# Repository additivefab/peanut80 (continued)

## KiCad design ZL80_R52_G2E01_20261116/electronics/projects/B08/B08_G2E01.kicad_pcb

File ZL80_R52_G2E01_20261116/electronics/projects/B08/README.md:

# B08 G2-E01

打开 B08_G2E01.kicad_pro。原理图是元件级候选；PCB有板框/孔/封装/网络及初排，尚无布线。

- Preserves R51 four-pin interface; bipolar supply required.
- Photodiode nominal reverse bias 5V. Current into cathode is sunk to negative bias; output is positive.
- 0..100uA input corresponds approximately 0..1V output. Confirm pickoff power before connecting.
- RF=10k / CF=100p is a ~159kHz feedback pole; reference and PMT channel delays must be aligned.
- This reference signal feeds B02 channel B through its own FDA; not directly a differential ADC input.

状态：NOT_RELEASED。仿真为有限模型证据；没有台架结果。

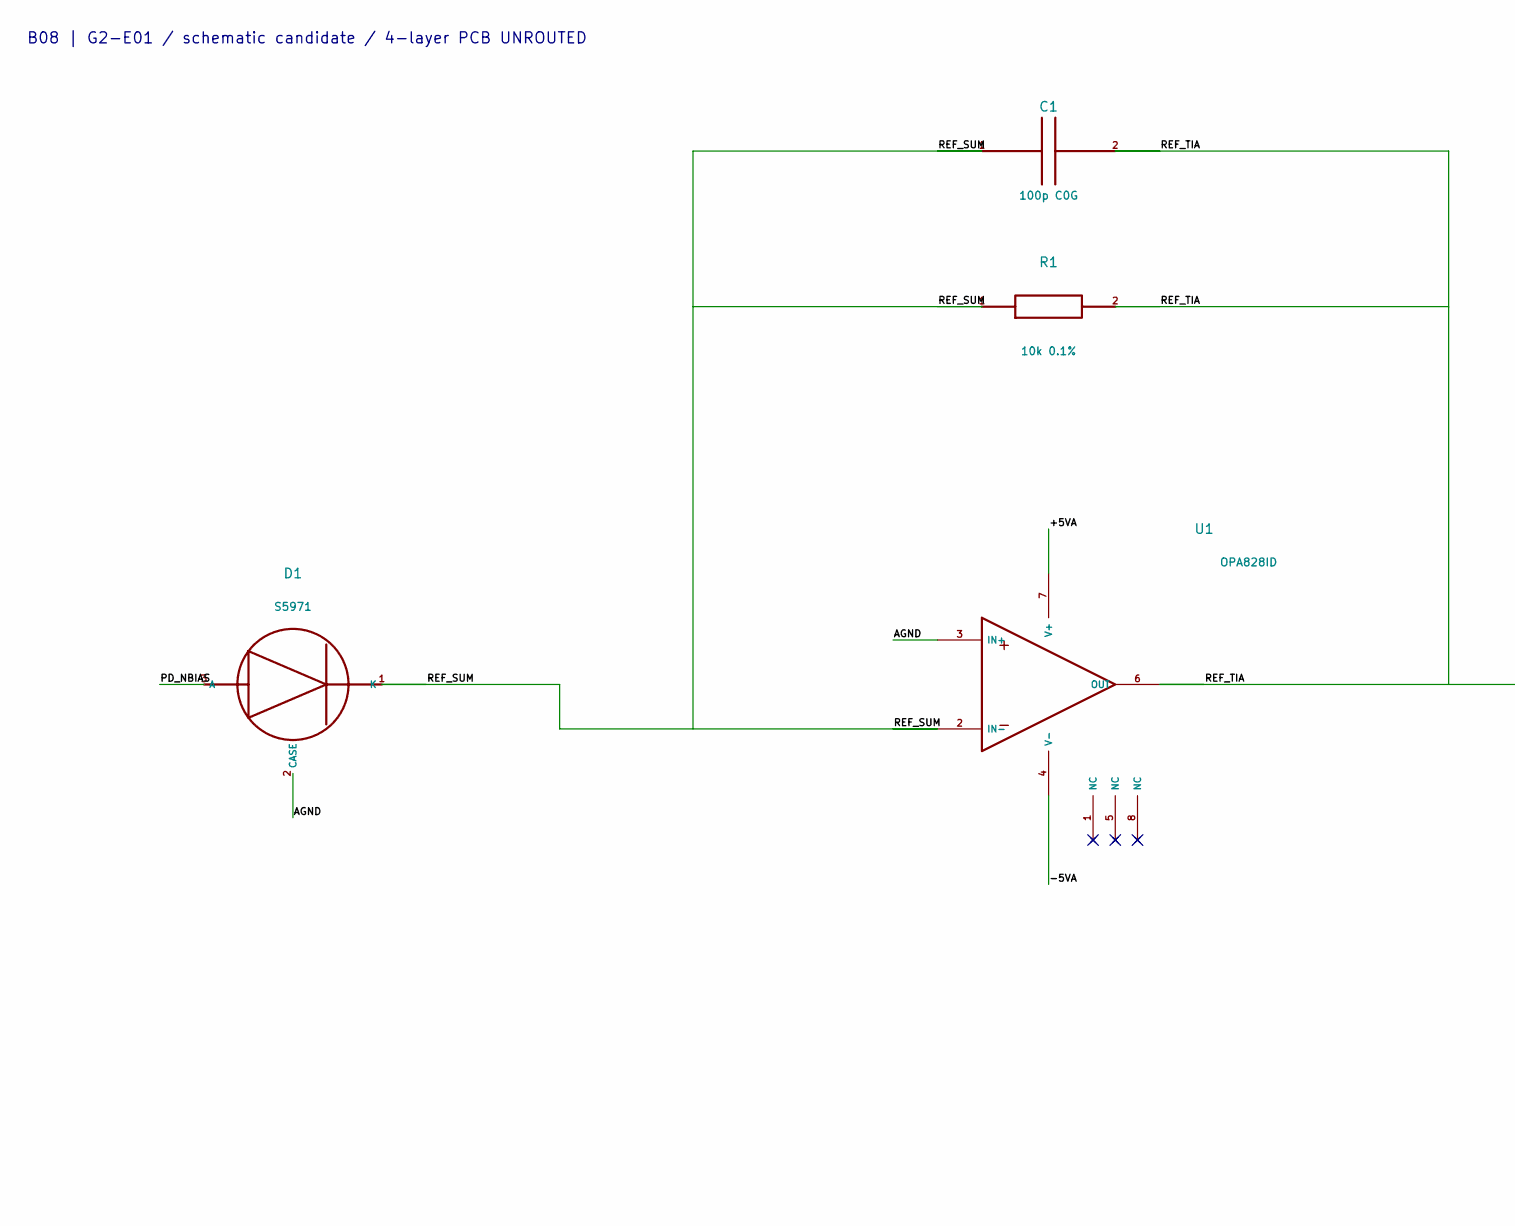
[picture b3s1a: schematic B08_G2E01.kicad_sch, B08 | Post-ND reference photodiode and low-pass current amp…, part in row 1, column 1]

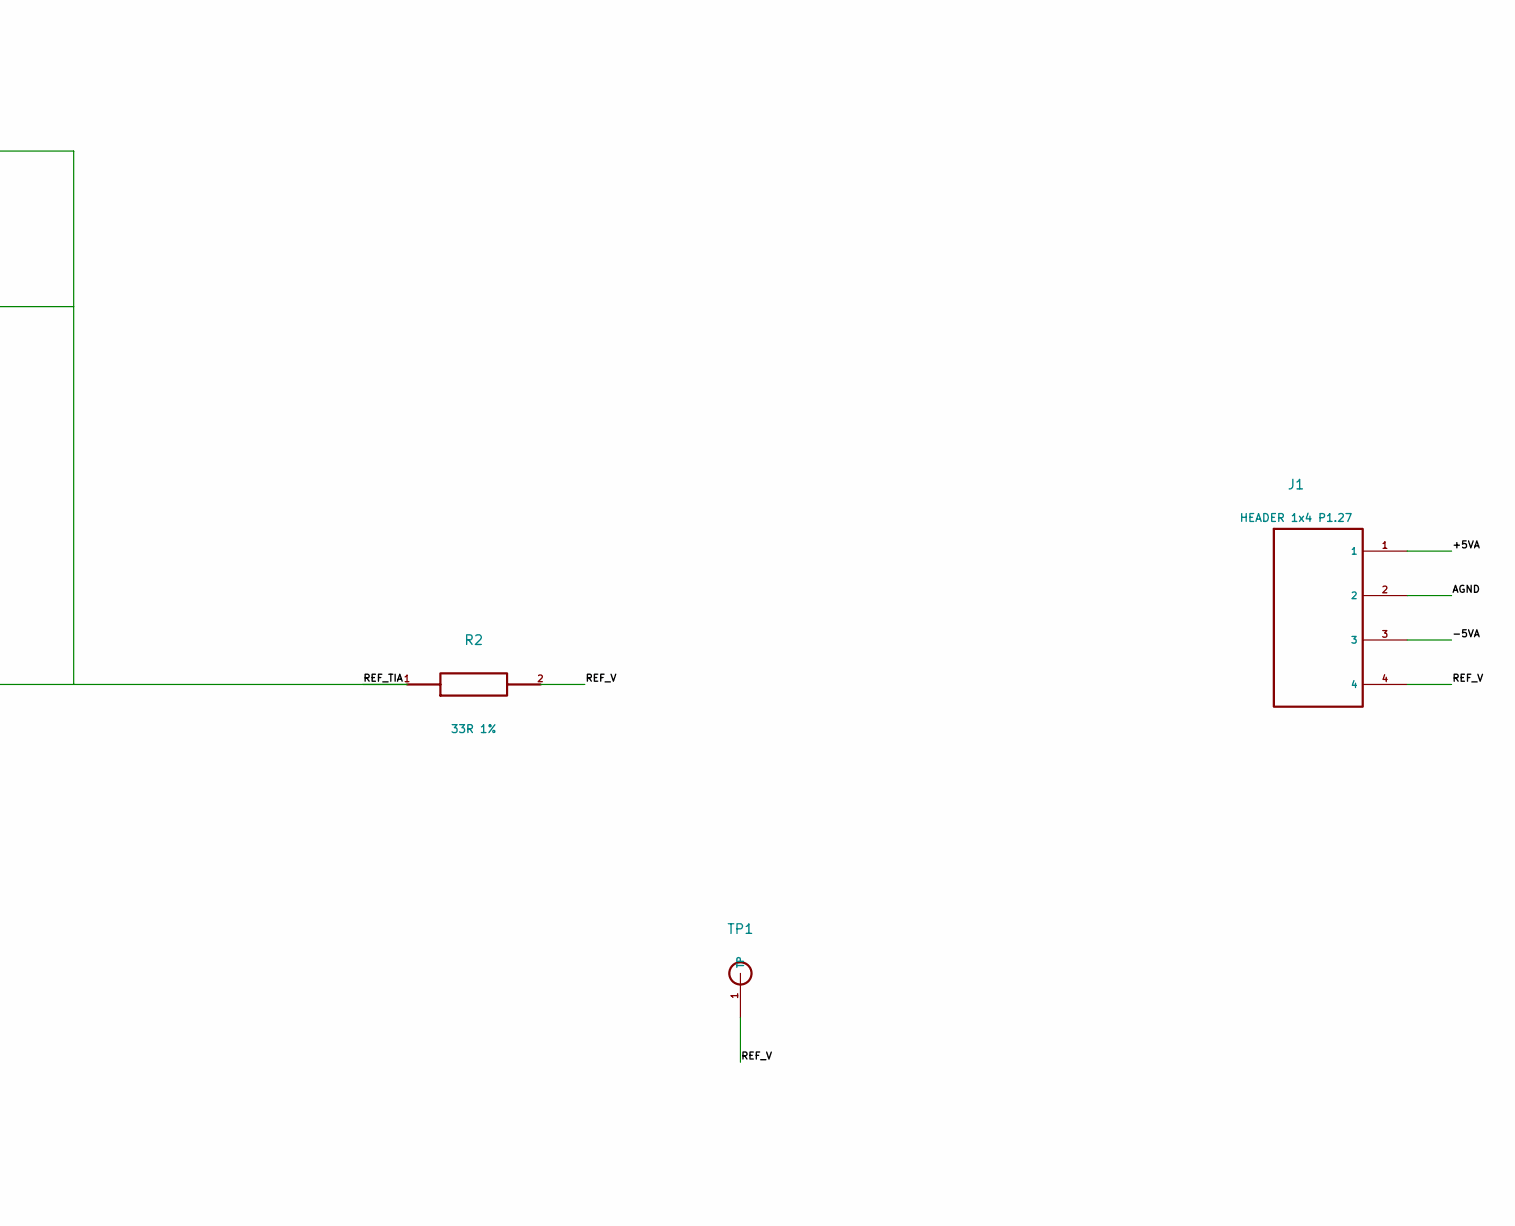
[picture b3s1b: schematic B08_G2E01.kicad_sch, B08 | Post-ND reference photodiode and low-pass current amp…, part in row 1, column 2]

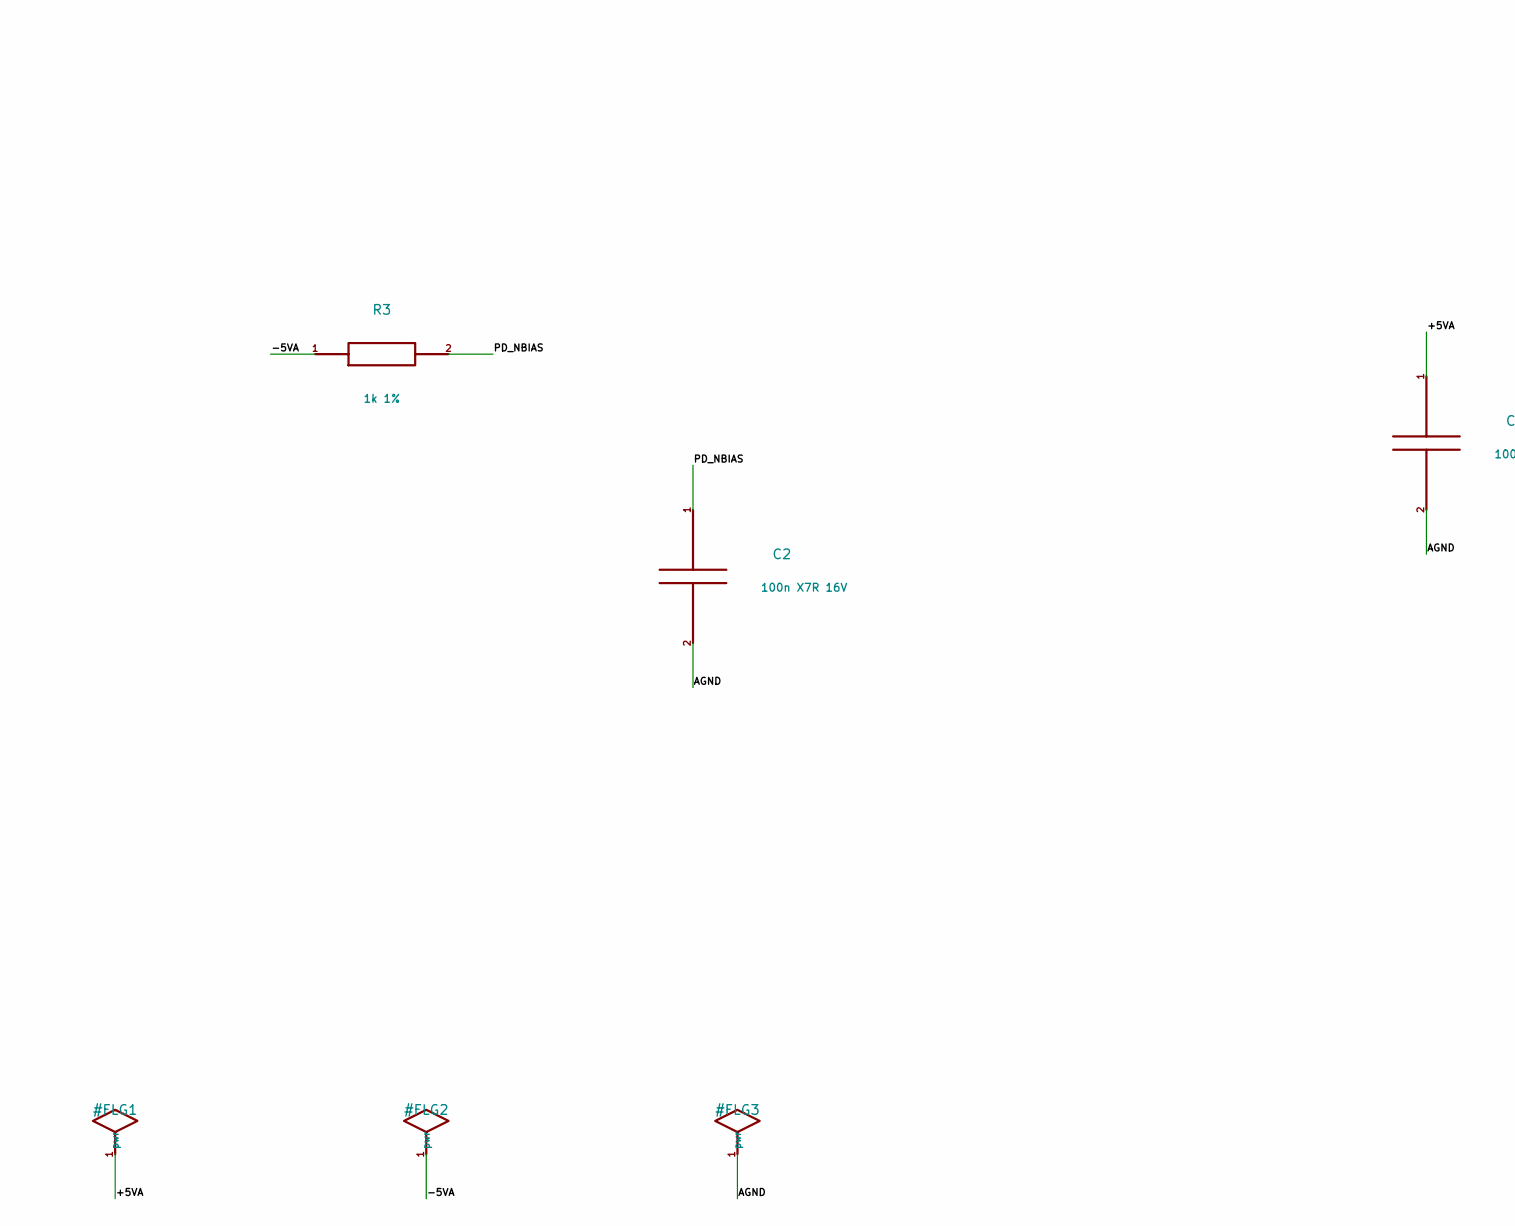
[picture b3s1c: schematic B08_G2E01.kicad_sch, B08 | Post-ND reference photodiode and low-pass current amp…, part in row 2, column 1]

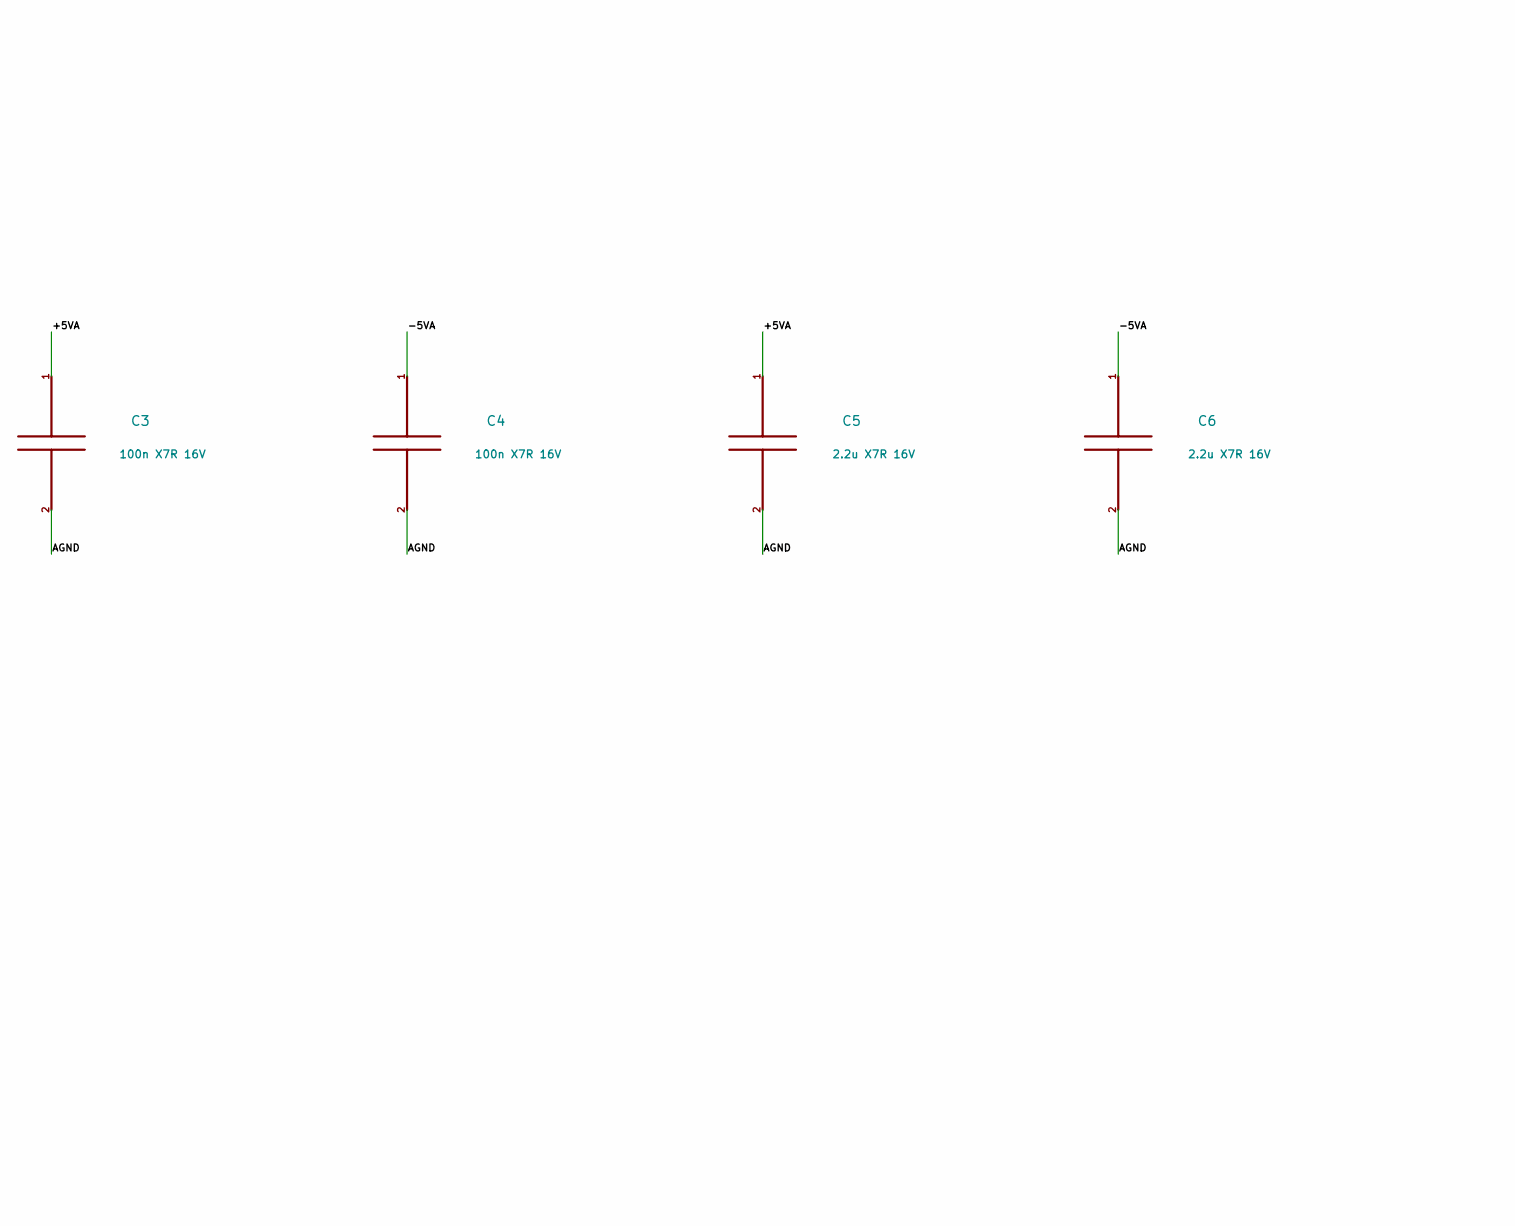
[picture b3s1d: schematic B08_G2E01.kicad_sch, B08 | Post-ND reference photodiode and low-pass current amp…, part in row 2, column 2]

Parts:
C1: 100p C0G; 0603
C2, C3, C4: 100n X7R 16V; 0603
C5, C6: 2.2u X7R 16V; 0603
D1: S5971; S5971_TO18_TOP; ManufacturerPartNumber S5971
J1: HEADER 1x4 P1.27; HDR4
R1: 10k 0.1%; 0603
R2: 33R 1%; 0603
R3: 1k 1%; 0603
TP1: REF_V; TP1
U1: OPA828ID; SOIC8; ManufacturerPartNumber OPA828ID

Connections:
+5VA: C3.1, C5.1, J1.1, U1.7 (V+)
-5VA: C4.1, C6.1, J1.3, R3.1, U1.4 (V-)
AGND: C2.2, C3.2, C4.2, C5.2, C6.2, D1.2 (CASE), J1.2, U1.3 (IN+)
PD_NBIAS: C2.1, D1.3 (A), R3.2
REF_SUM: C1.1, D1.1 (K), R1.1, U1.2 (IN-)
REF_TIA: C1.2, R1.2, R2.1, U1.6 (OUT)
REF_V: J1.4, R2.2, TP1.1

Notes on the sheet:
B08 | G2-E01 / schematic candidate / 4-layer PCB UNROUTED

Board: 4 copper layers, 17 parts (0 on the bottom side), 7 nets, no tracks yet.

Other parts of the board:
H1, H2, H3, H4: NPTH

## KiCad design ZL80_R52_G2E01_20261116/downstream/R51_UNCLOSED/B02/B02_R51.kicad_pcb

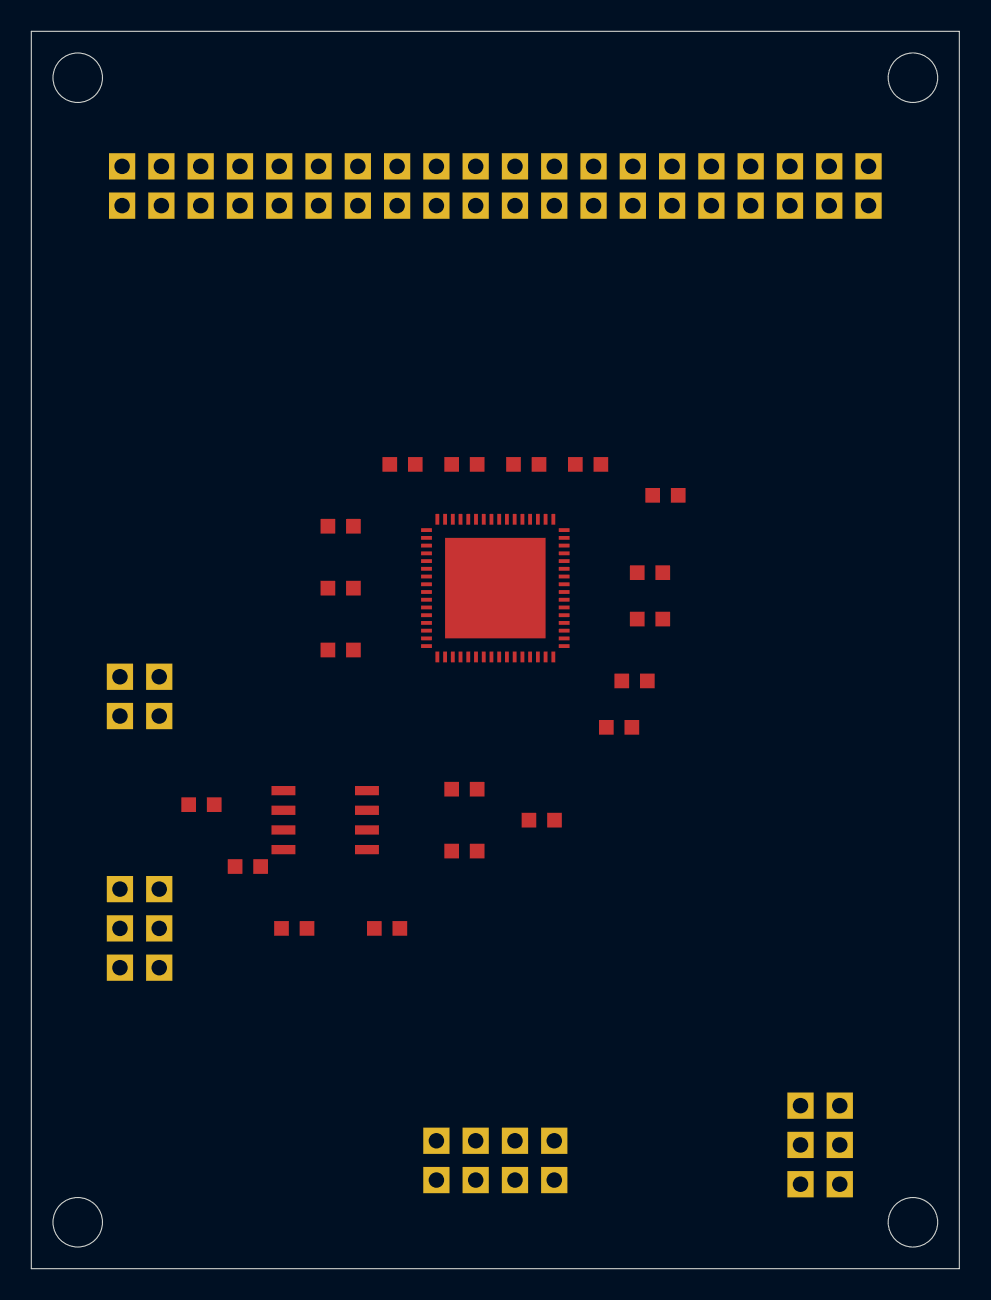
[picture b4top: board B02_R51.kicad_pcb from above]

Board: 6 copper layers, 60.0 x 80.0 mm, 32 parts (0 on the bottom side), 52 nets, no tracks yet.

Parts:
C1: 330p_DIFF_TRIAL; B02_C1
C2: 1u; B02_C2
C3: 100n; B02_C3
C4: 100n; B02_C4
C5: 100n; B02_C5
C6: 100n; B02_C6
C7: 100n; B02_C7
C8: 100n; B02_C8
C9: 100n; B02_C9
C10: 100n; B02_C10
C11: 100n; B02_C11
J1: HEADER_2x20_P2.54; B02_J1
J2: HEADER_2x3_P2.54; B02_J2
J3: HEADER_2x2_P2.54; B02_J3
J4: HEADER_2x4_P2.54; B02_J4
J5: HEADER_2x3_P2.54; B02_J5
MH1, MH2, MH3, MH4: NPTH; MountingHole_3.2
R1: 499; B02_R1
R2: 499; B02_R2
R3: 499; B02_R3
R4: 499; B02_R4
R5: 33R; B02_R5
R6: 33R; B02_R6
R7: 10k_1%; B02_R7
R8: 0R; B02_R8
U1: AD9268BCPZ-80; B02_U1
U2: AD8138ARZ; B02_U2
U3: SPI_3V3_1V8_TRANSLATOR_RFQ; B02_U3
Y1: 20MHz_1V8_OSC_RFQ; B02_Y1

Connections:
1V8A: C5.1, C7.1, C9.1, C11.1, J5.1, U1.49, U1.50, U1.53, U1.54, U1.59, U1.60, U1.63, U1.64
1V8D: C4.1, C6.1, C8.1, C10.1, J5.3, U1.10, U1.19, U1.28, U1.37
+5VA: J5.5, U2.3
-5VA: J5.6, U2.6
ADC_A_N: J2.3, U1.52
ADC_A_P: J2.1, U1.51
ADC_B_N: C1.2, R6.2, U1.61
ADC_B_P: C1.1, R5.2, U1.62
ADC_RBIAS: R7.1, U1.58
ADC_SENSE: R8.1, U1.56
ADC_VCM: J2.5, U1.57, U2.2
ADC_VREF: C2.1, C3.1, U1.55
AGND: C2.2, C3.2, C4.2, C5.2, C6.2, C7.2, C8.2, C9.2, C10.2, C11.2, J1.35, J1.36, J2.2, J2.4, J2.6, J3.2, J3.4, J4.2, J5.2, J5.4, R3.1, R7.2, R8.2, U1.65
DA0: J1.1, U1.25
DA1: J1.2, U1.26
DA2: J1.3, U1.27
DA3: J1.4, U1.29
DA4: J1.5, U1.30
DA5: J1.6, U1.31
DA6: J1.7, U1.32
DA7: J1.8, U1.33
DA8: J1.9, U1.34
DA9: J1.10, U1.35
DA10: J1.11, U1.36
DA11: J1.12, U1.38
DA12: J1.14, U1.39
DA13: J1.15, U1.40
DA14: J1.16, U1.41
DA15: J1.18, U1.42
DB0: J1.19, U1.4
DB1: J1.20, U1.5
DB2: J1.21, U1.6
DB3: J1.22, U1.7
DB4: J1.23, U1.8
DB5: J1.24, U1.9
DB6: J1.25, U1.11
DB7: J1.26, U1.12
DB8: J1.27, U1.13
DB9: J1.28, U1.14
DB10: J1.29, U1.15
DB11: J1.30, U1.16
DB12: J1.31, U1.17
DB13: J1.32, U1.18
DB14: J1.33, U1.20
DB15: J1.34, U1.21
DCOA: J1.13, U1.24
DCOB: J1.17, U1.23
D_B_N: R2.1, R6.1, U2.5
D_B_P: R4.1, R5.1, U2.4
REF_FDA_N: R3.2, R4.2, U2.1
REF_FDA_P: R1.2, R2.2, U2.8
REF_V: J3.1, J3.3, R1.1
